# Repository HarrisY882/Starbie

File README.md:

# My Starbie Project
using hack club half life, my alternative version of starbie, is inspired by the among us characters, something id randomly thought of, Starbie was actually a pretty cool idea, im glad that its something fun that i would be intrested in using.

I think during this project, i got to understand KICAD ALOT more, for exmaple i never even knew about datasheets and how to find corresponding foortprints, ive found that i actually enjoy it alot more aswell.

This is a schematic picture. I also found it intresting that you could use a basic 1_4 connection pin point, that definetly took me while to get the hang off.

Friday 9th October -12:04
 Alright, so far ive started to learn pcb design, as of yet ive designed a pcb, this was actually a really good guide,  now i for sure know how to make a schematic, at first i thought everything had to be connected to each other, and now i know how to turn it into a pcb design, and solving issues, like the courtyard error, showed me lots of feats that were included in kicad. Footprints are important. I just need to improve on how to find the actual footprints and components for exmaple by looking at a datasheet.

as you can see this is my pcb design, my only worry is the shape looks abit dodgy, but surely i can file it down, that is if it can be made.

in the future i hope to be able to code more, something i stuggled with here, as i was mostly trying to understand the code, and didnt write much only a little.

| Item                                        | Qty | Supplier     | Cost/item | Total Cost | Link                                                                                                    |
| ------------------------------------------- | --- | ------------ | --------- | ---------- | ------------------------------------------------------------------------------------------------------- |
| XIAO ESP32-C3                               | 1   | Seeed Studio | $4.90     | $4.90      | [Seeed Studio](https://www.seeedstudio.com/Seeed-XIAO-ESP32C3-p-5431.html?utm_source=chatgpt.com)       |
| DHT11 Temperature & Humidity Sensor Module  | 1   | ElectroPeak  | $0.50     | $0.50      | [ElectroPeak](https://electropeak.com/temprature-sensor-dht11-dfrobot-1?utm_source=chatgpt.com)         |
| 0.96-inch I²C OLED Display Module (SSD1306) | 1   | ElectroPeak  | $0.96     | $0.96      | [ElectroPeak](https://electropeak.com/0-96-inch-i2c-oled-display-module-ssd1306?utm_source=chatgpt.com) |
| MPU6050 Gyroscope & Accelerometer           | 1   | ElectroPeak  | $1.47     | $1.47      | [ElectroPeak](https://electropeak.com/gyro-accelerometer-gy521-mpu6050?utm_source=chatgpt.com)          |
| PCB                                         | 1   | PCBWay       | $5.00     | $5.00      | [PCBWay](https://www.pcbway.com/QuickOrderOnline.aspx?utm_source=chatgpt.com)                           |
| Subtotal (Items)                            |     |              |           | $12.83     |                                                                                                         |
| Estimated Shipping                          |     |              |           | $17.13     |                                                                                                         |
| Grand Total (Items + Shipping)              |     |              |           | $29.96     |                                                                                                         |

Cost summary

- Total component and PCB cost: $12.83
- Estimated shipping cost: $17.13
- Total estimated cost: $29.96

this is a 3d render of my pcb showing how it would actually look when pcb is printed and where components would go.

**i didnt use ai for the project the only place was creating the BOM table above,**
thanks for reading.

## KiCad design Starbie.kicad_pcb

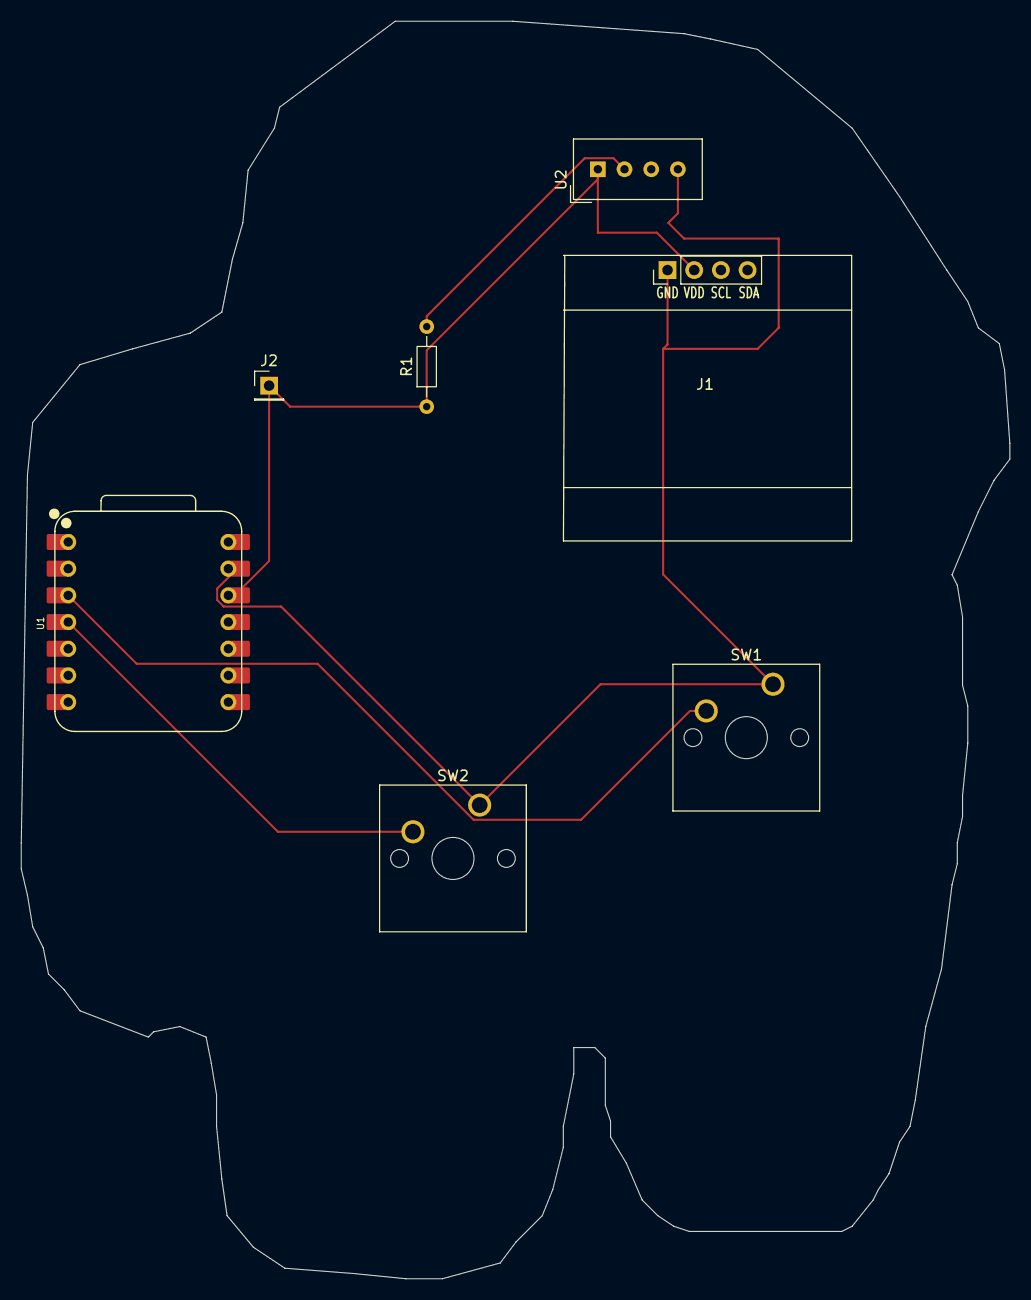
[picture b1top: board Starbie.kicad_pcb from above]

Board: 2 copper layers, 94.1 x 119.7 mm, 7 parts (0 on the bottom side), 5 nets.

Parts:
J1: Conn_01x04_Pin; Display_128x64_096_I2C
J2: Conn_01x08_Pin; PinHeader_1x01_P2.54mm_Vertical
R1: 10k; R_Axial_DIN0204_L3.6mm_D1.6mm_P7.62mm_Horizontal
SW1, SW2: SW_Push; SW_Cherry_MX_1.00u_PCB
U1: XIAO-ESP32-C3-SMD; XIAO-ESP32-C6-DIP
U2: DHT11; Aosong_DHT11_5.5x12.0_P2.54mm

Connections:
+3.3V: J1.2, J2.1 (Pin_1_1), R1.1, U1.12 (3V3_OUT), U2.1 (VDD)
GND: J1.1, SW1.1, SW2.1, U1.13 (GND), U2.4 (GND)
unnamed: SW1.2, U1.3 (D2)
unnamed: SW2.2, U1.4 (D3)
unnamed: R1.2, U2.2 (DATA)
